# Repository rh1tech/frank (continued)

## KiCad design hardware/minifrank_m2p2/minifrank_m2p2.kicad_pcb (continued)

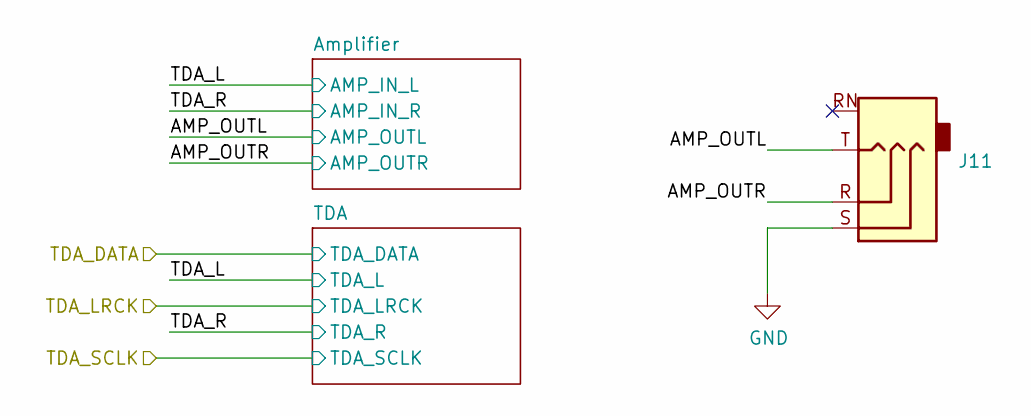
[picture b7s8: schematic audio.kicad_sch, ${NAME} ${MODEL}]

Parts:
J11: PJ-320D; Jack (3.5mm, PJ-320D)

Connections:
/Audio/AMP_OUTL: J11.T; also elsewhere on the board
/Audio/AMP_OUTR: J11.R; also elsewhere on the board
GND: J11.S; also elsewhere on the board

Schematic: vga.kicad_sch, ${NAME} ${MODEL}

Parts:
J10: VGA; D-SUB (15 pin, female)
R28, R29, R30: 330R; R_0603_1608Metric
R31, R32, R33: 1K; R_0603_1608Metric
R34, R35: 100R; R_0603_1608Metric

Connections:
/GPIO12: R33.1; also elsewhere on the board
/GPIO13: R30.1; also elsewhere on the board
/GPIO14: R32.1; also elsewhere on the board
/GPIO15: R29.1; also elsewhere on the board
/GPIO16: R31.1; also elsewhere on the board
/GPIO17: R28.1; also elsewhere on the board
/GPIO18: R34.2; also elsewhere on the board
/GPIO19: R35.2; also elsewhere on the board
GND: J10.0, J10.5, J10.6, J10.7, J10.8, J10.10; also elsewhere on the board
unnamed: J10.1, R28.2, R31.2
unnamed: J10.2, R29.2, R32.2
unnamed: J10.3, R30.2, R33.2
unnamed: J10.13, R34.1
unnamed: J10.14, R35.1

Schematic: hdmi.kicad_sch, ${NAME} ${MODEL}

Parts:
C24: 100n; C_0603_1608Metric
D1: 1N5819WS; Diode (SOD-323)
J8: DC3RX19JA2; HDMI (female)
RN1, RN2: 270R; Resistor Array (4x0603)

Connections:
/GPIO12: RN1.4 (R4.1); also elsewhere on the board
/GPIO13: RN1.3 (R3.1); also elsewhere on the board
/GPIO14: RN1.2 (R2.1); also elsewhere on the board
/GPIO15: RN1.1 (R1.1); also elsewhere on the board
/GPIO16: RN2.4 (R4.1); also elsewhere on the board
/GPIO17: RN2.3 (R3.1); also elsewhere on the board
/GPIO18: RN2.2 (R2.1); also elsewhere on the board
/GPIO19: RN2.1 (R1.1); also elsewhere on the board
GND: C24.2, J8.2 (G_D2), J8.5 (G_D1), J8.8 (G_D0), J8.11 (G_CLK), J8.17 (G_DDC/CEC), J8.20 (SHIELD1), J8.21 (SHIELD2), J8.22 (SHIELD3), J8.23 (SHIELD4); also elsewhere on the board
unnamed: C24.1, D1.1 (K), J8.18 (+5V)
unnamed: J8.12 (CLKN), RN1.5 (R4.2)
unnamed: J8.10 (CLKP), RN1.6 (R3.2)
unnamed: J8.9 (D0N), RN1.7 (R2.2)
unnamed: J8.7 (D0P), RN1.8 (R1.2)
unnamed: J8.6 (D1N), RN2.5 (R4.2)
unnamed: J8.4 (D1P), RN2.6 (R3.2)
unnamed: J8.3 (D2N), RN2.7 (R2.2)
unnamed: J8.1 (D2P), RN2.8 (R1.2)
VBUS: D1.2 (A); also elsewhere on the board

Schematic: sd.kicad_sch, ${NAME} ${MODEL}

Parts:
C43: 100n; C_0603_1608Metric
J12: 104031-0811; MicroSD (SMD, long)

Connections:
+3V3: C43.2, J12.4 (VDD); also elsewhere on the board
/GPIO4: J12.7 (DAT0); also elsewhere on the board
/GPIO5: J12.2 (DAT3/CD); also elsewhere on the board
/GPIO6: J12.5 (CLK); also elsewhere on the board
/GPIO7: J12.3 (CMD); also elsewhere on the board
GND: C43.1, J12.6 (VSS); also elsewhere on the board

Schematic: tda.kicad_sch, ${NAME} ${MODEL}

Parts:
C33, C35: 10u; C_0603_1608Metric
C34: 100n; C_0603_1608Metric
R36: 100R; R_0603_1608Metric
R37, R38: 470R; R_0603_1608Metric
U11: TDA1387T; SO-8

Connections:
/Audio/TDA_L: R38.2, U11.6 (A_LEFT); also elsewhere on the board
/Audio/TDA_R: R37.1, U11.8 (A_RIGHT); also elsewhere on the board
/GPIO9: U11.3 (DATA); also elsewhere on the board
/GPIO10: U11.1 (SCLK); also elsewhere on the board
/GPIO11: U11.2 (LRCK); also elsewhere on the board
GND: C33.2, C34.2, C35.2, R37.2, R38.1, U11.4 (AGND); also elsewhere on the board
unnamed: C35.1, U11.7 (FLT)
unnamed: C33.1, C34.1, R36.1, U11.5 (VA)
VBUS: R36.2; also elsewhere on the board

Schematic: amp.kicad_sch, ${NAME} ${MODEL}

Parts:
C36, C37, C38, C40, C41: 10u; C_0603_1608Metric
C39: 10u; Capacitor (3528, tantalum, polar)
C42: 100n; C_0603_1608Metric
R39, R40, R41, R42, R43, R44: 10K; R_0603_1608Metric
R45, R46: 47K; R_0603_1608Metric
R47, R48: 20K; R_0603_1608Metric
R49: 100R; R_0603_1608Metric
U12: LM358; SO-8

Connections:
/Audio/AMP_OUTL: C40.2, R47.2; also elsewhere on the board
/Audio/AMP_OUTR: C41.2, R48.2; also elsewhere on the board
/Audio/TDA_L: C36.1, R39.1; also elsewhere on the board
/Audio/TDA_R: C37.1, R40.1; also elsewhere on the board
GND: C38.1, C39.2, C42.1, R39.2, R40.2, R42.1, R47.1, R48.1, U12.4 (V-); also elsewhere on the board
unnamed: C36.2, R43.2
unnamed: C37.2, R44.2
unnamed: C40.1, R45.1, U12.7
unnamed: C41.1, R46.1, U12.1
unnamed: C38.2, R41.1, R42.2, U12.3 (+), U12.5 (+)
unnamed: R44.1, R46.2, U12.2 (-)
unnamed: R43.1, R45.2, U12.6 (-)
unnamed: C39.1, C42.2, R41.2, R49.2, U12.8 (V+)
VBUS: R49.1; also elsewhere on the board

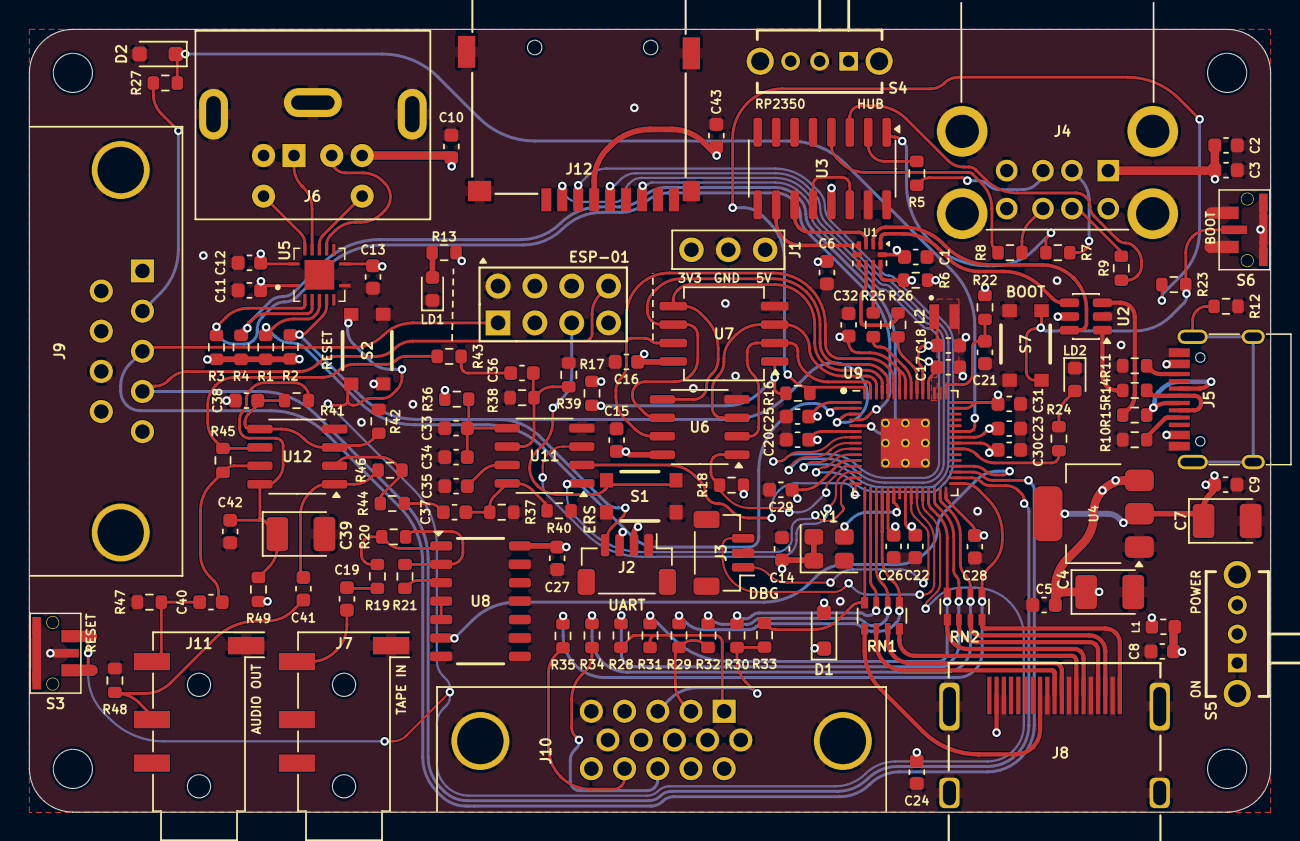
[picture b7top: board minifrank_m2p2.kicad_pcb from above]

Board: 4 copper layers, 85.6 x 54.0 mm, 136 parts (0 on the bottom side), 112 nets.
